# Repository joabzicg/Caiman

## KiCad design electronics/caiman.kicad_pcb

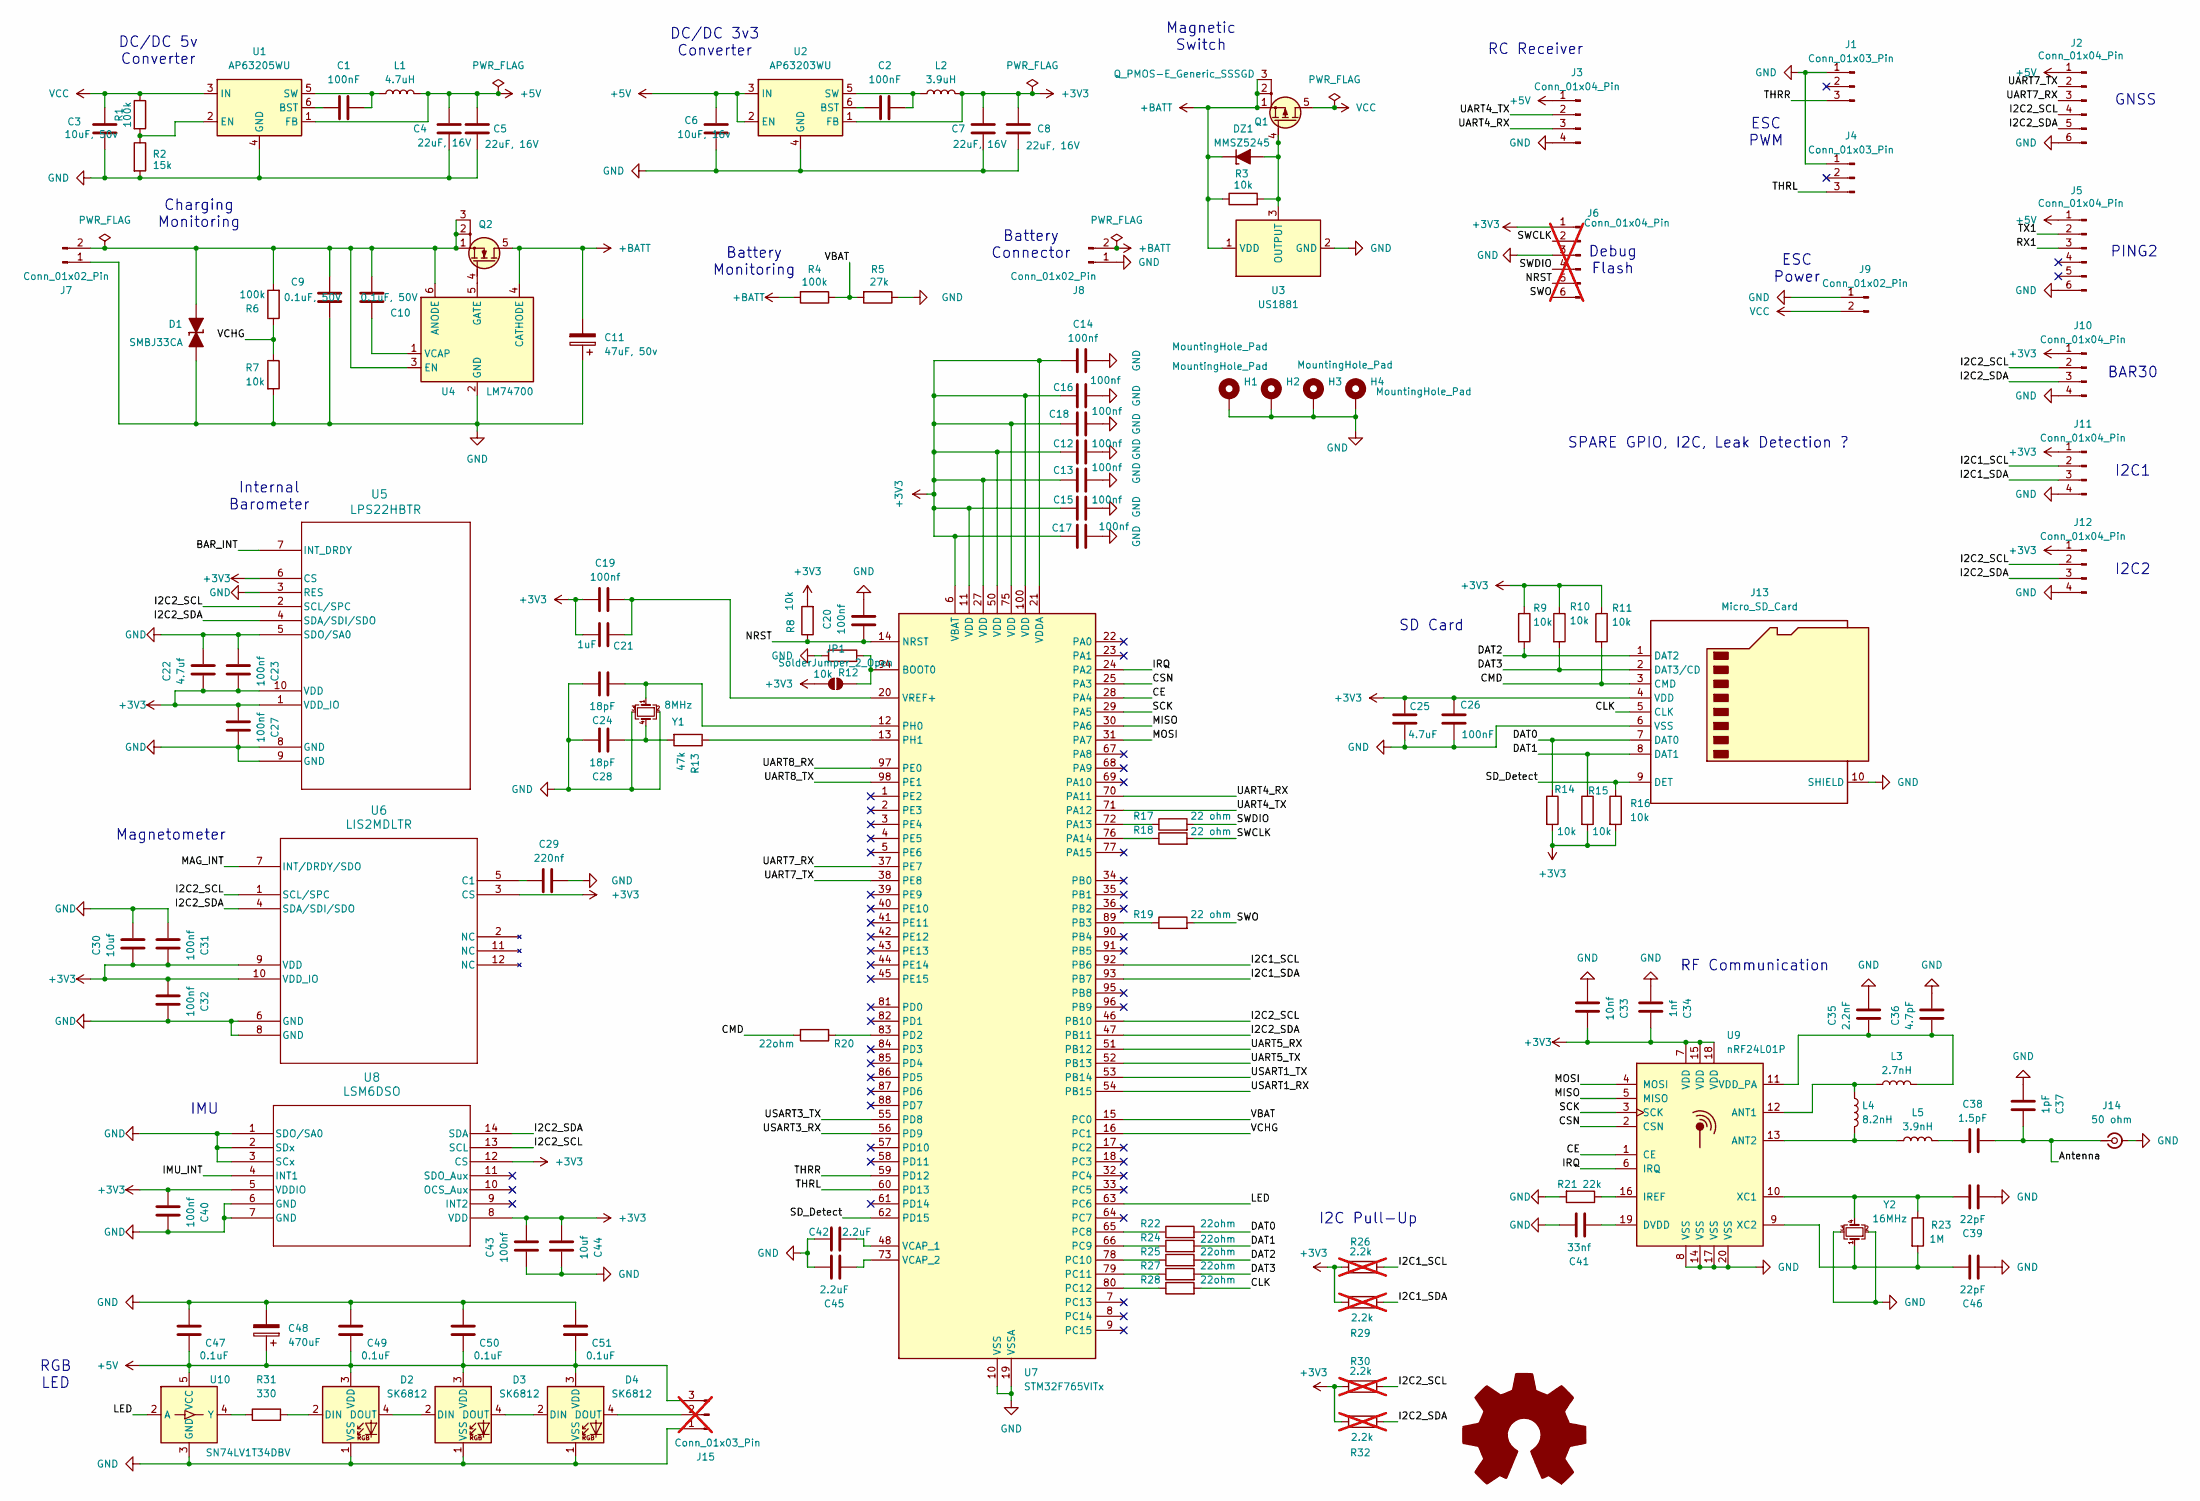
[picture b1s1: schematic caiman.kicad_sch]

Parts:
C1, C2: 100nF; C_0603_1608Metric
C3: 10uF, 50v; C_0805_2012Metric
C4, C5, C7, C8: 22uF, 16V; C_0603_1608Metric
C6: 10uF, 16v; C_0805_2012Metric
C9, C10: 0.1uF, 50V; C_0805_2012Metric
C11: 47uF, 50v; CP_Elec_8x10; Mouser 581-AEA0810470M063R
C12, C13, C14, C15, C16, C17, C18, C19, C20, C23, C27, C31, C32, C40, C43: 100nf; C_0402_1005Metric
C21: 1uF; C_0402_1005Metric
C22: 4.7uf; C_0402_1005Metric
C24, C28: 18pF; C_0402_1005Metric
C25: 4.7uF; C_0402_1005Metric
C26: 100nF; C_0402_1005Metric
C29: 220nf; C_0402_1005Metric
C30, C44: 10uf; C_0402_1005Metric
C33: 10nf; C_0402_1005Metric
C34: 1nf; C_0402_1005Metric
C35: 2.2nF; C_0402_1005Metric
C36: 4.7pF; C_0402_1005Metric
C37: 1pF; C_0402_1005Metric
C38: 1.5pF; C_0402_1005Metric
C39, C46: 22pF; C_0402_1005Metric
C41: 33nf; C_0402_1005Metric
C42, C45: 2.2uF; C_0402_1005Metric
C47, C49, C50, C51: 0.1uF; C_0603_1608Metric
C48: 470uF; CP_Elec_8x10; Mouser 581-AEA0810471M016R
D1: SMBJ33CA; D_SMB_TVS; Mouser 652-SMBJ33CA
D2, D3, D4: SK6812; LED_SK6812_PLCC4_5.0x5.0mm_P3.2mm; Mouser 485-4691
DZ1: MMSZ5245; D_SOD-123F_Zener
H1, H2, H3, H4: MountingHole_Pad; MountingHole_4.3mm_M4_ISO7380_Pad_TopBottom
J1, J4: Conn_01x03_Pin; PinHeader_1x03_P2.54mm_Vertical
J2, J5: Conn_01x04_Pin; JST_GH_BM06B-GHS-TBT_1x06-1MP_P1.25mm_Vertical; Mouser 306-BM06BGHSTBTLFSNN
J3, J10, J11, J12: Conn_01x04_Pin; JST_GH_BM04B-GHS-TBT_1x04-1MP_P1.25mm_Vertical; Mouser 306-BM04BGHSTBTLFSNN
J6: Conn_01x04_Pin; PinHeader_1x06_P2.54mm_Vertical; not fitted
J7: Conn_01x02_Pin; AMASS_XT30UPB-M_1x02_P5.0mm_Vertical; Mouser 426-FIT0587
J8: Conn_01x02_Pin; AMASS_XT60-M_1x02_P7.20mm_Vertical; Mouser 426-FIT0587
J9: Conn_01x02_Pin; AMASS_XT60-F_1x02_P7.20mm_Vertical; Mouser 426-FIT0587
J13: Micro_SD_Card; microSD_HC_Hirose_DM3AT-SF-PEJM5; Mouser 798-DM3ATSFPEJM511
J14: 50 ohm; U.FL_Hirose_U.FL-R-SMT-1_Vertical
J15: Conn_01x03_Pin; PinHeader_1x03_P2.54mm_Vertical; not fitted
JP1: SolderJumper_2_Open; SolderJumper-2_P1.3mm_Open_TrianglePad1.0x1.5mm
L1: 4.7uH; L_Wuerth_MAPI-4020; Mouser 652-SRP4020FA-3R3M
L2: 3.9uH; L_Wuerth_MAPI-4020; Mouser 652-SRP4020FA-2R2M
L3: 2.7nH; L_0402_1005Metric
L4: 8.2nH; L_0402_1005Metric
L5: 3.9nH; L_0402_1005Metric
Q1: Q_PMOS-E_Generic_SSSGD; PowerPAK_SO-8L_Single; Mouser 78-SQJ457EP-T1_GE3
Q2: AON6262E; TDSON-8-1; Digikey 800-3747-2-ND
R1, R4, R6: 100k; R_0603_1608Metric
R2: 15k; R_0603_1608Metric
R3, R7: 10k; R_0603_1608Metric
R5: 27k; R_0603_1608Metric
R8, R9, R10, R11, R12, R14, R15, R16: 10k; R_0402_1005Metric
R13: 47k; R_0402_1005Metric
R17, R18, R19: 22 ohm; R_0402_1005Metric
R20, R22, R24, R25, R27, R28: 22ohm; R_0402_1005Metric
R21: 22k; R_0402_1005Metric
R23: 1M; R_0402_1005Metric
R26, R29, R30, R32: 2.2k; R_0402_1005Metric; not fitted
R31: 330; R_0603_1608Metric
U1: AP63205WU; TSOT-23-6; Mouser 621-AP63205WU-7
U2: AP63203WU; TSOT-23-6; Mouser 621-AP63203WU-7
U3: US1881; TO-92; Mouser 482-1881LUAAAA000BU
U4: LM74700; SOT-23-6; Mouser 595-LM74700QDBVRQ1
U5: LPS22HBTR; ST_HLGA-10_2x2mm_P0.5mm_LayoutBorder3x2y
U6: LIS2MDLTR; LGA-12_2x2mm_P0.5mm
U7: STM32F765VITx; LQFP-100_14x14mm_P0.5mm
U8: LSM6DSO; LGA-14_3x2.5mm_P0.5mm_LayoutBorder3x4y
U9: nRF24L01P; QFN-20-1EP_4x4mm_P0.5mm_EP2.5x2.5mm
U10: SN74LV1T34DBV; SOT-23-5; Mouser 595-SN74LV1T34DBVRG4
Y1: 8MHz; Crystal_SMD_3225-4Pin_3.2x2.5mm
Y2: 16MHz; Crystal_SMD_3225-4Pin_3.2x2.5mm

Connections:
+3V3: C7.2, C8.2, C12.2, C13.2, C14.2, C15.2, C16.2, C17.2, C18.2, C19.2, C21.2, C22.1, C23.1, C25.1, C26.1, C27.2, C30.1, C31.1, C32.2, C33.1, C34.1, C40.2, C43.2, C44.2, J6.1, J10.1, J11.1, J12.1, J13.4 (VDD), JP1.1 (A), L2.2, R8.2, R9.1, R10.1, R11.1, R14.2, R15.2, R16.2, R26.1, R29.1, R30.1, R32.1, U2.1 (FB), U5.1 (VDD_IO), U5.6 (CS), U5.10 (VDD), U6.3 (CS), U6.9 (VDD), U6.10 (VDD_IO), U7.6 (VBAT), U7.11 (VDD), U7.21 (VDDA), U7.27 (VDD), U7.50 (VDD), U7.75 (VDD), U7.100 (VDD), U8.5 (VDDIO), U8.8 (VDD), U8.12 (CS), U9.7 (VDD), U9.15 (VDD), U9.18 (VDD)
+5V: C4.2, C5.2, C6.2, C47.2, C48.1, C49.2, C50.2, C51.2, D2.3 (VDD), D3.3 (VDD), D4.3 (VDD), J2.1, J3.1, J5.1, J15.3, L1.2, U1.1 (FB), U2.2 (EN), U2.3 (IN), U10.5 (VCC)
+BATT: C11.2, DZ1.1 (K), J8.2, Q1.1 (S), Q1.2 (S), Q1.3 (S), Q2.5 (D), R3.1, R4.2, U3.1 (VDD), U4.4 (CATHODE)
/Antenna: C37.2, C38.2, J14.1 (In)
/BAR_INT: U5.7 (INT_DRDY)
/CE: U7.28 (PA4), U9.1 (CE)
/CLK: J13.5 (CLK), R28.2
/CMD: J13.3 (CMD), R11.2, R20.2
/CSN: U7.25 (PA3), U9.2 (CSN)
/DAT0: J13.7 (DAT0), R14.1, R22.2
/DAT1: J13.8 (DAT1), R15.1, R24.2
/DAT2: J13.1 (DAT2), R9.2, R25.2
/DAT3: J13.2 (DAT3/CD), R10.2, R27.2
/I2C1_SCL: J11.2, R26.2, U7.92 (PB6)
/I2C1_SDA: J11.3, R29.2, U7.93 (PB7)
/I2C2_SCL: J2.4, J10.2, J12.2, R30.2, U5.2 (SCL/SPC), U6.1 (SCL/SPC), U7.46 (PB10), U8.13 (SCL)
/I2C2_SDA: J2.5, J10.3, J12.3, R32.2, U5.4 (SDA/SDI/SDO), U6.4 (SDA/SDI/SDO), U7.47 (PB11), U8.14 (SDA)
/IMU_INT: U8.4 (INT1)
/IRQ: U7.24 (PA2), U9.6 (IRQ)
/LED: U7.63 (PC6), U10.2 (A)
/MAG_INT: U6.7 (INT/DRDY/SDO)
/MISO: U7.30 (PA6), U9.5 (MISO)
/MOSI: U7.31 (PA7), U9.4 (MOSI)
/NRST: C20.2, J6.5, R8.1, U7.14 (NRST)
/RX1: J5.3
/SCK: U7.29 (PA5), U9.3 (SCK)
/SD_Detect: J13.9 (DET), R16.1, U7.62 (PD15)
/SWCLK: J6.2, R18.2
/SWDIO: J6.4, R17.2
/SWO: J6.6, R19.2
/THRL: J4.3, U7.60 (PD13)
/THRR: J1.3, U7.59 (PD12)
/TX1: J5.2
/UART4_RX: J3.3, U7.70 (PA11)
/UART4_TX: J3.2, U7.71 (PA12)
/UART5_RX: U7.51 (PB12)
/UART5_TX: U7.52 (PB13)
/UART7_RX: J2.3, U7.37 (PE7)
/UART7_TX: J2.2, U7.38 (PE8)
/UART8_RX: U7.97 (PE0)
/UART8_TX: U7.98 (PE1)
/USART1_RX: U7.54 (PB15)
/USART1_TX: U7.53 (PB14)
/USART3_RX: U7.56 (PD9)
/USART3_TX: U7.55 (PD8)
/VBAT: R4.1, R5.2, U7.15 (PC0)
/VCHG: R6.1, R7.1, U7.16 (PC1)
unnamed: C38.1, L5.2
unnamed: C9.1, C10.2, D1.2 (A), J7.2, Q2.1 (S), Q2.2 (S), Q2.3 (S), R6.2, U4.3 (EN), U4.6 (ANODE)
unnamed: D2.2 (DIN), R31.2
unnamed: D2.4 (DOUT), D3.2 (DIN)
unnamed: D3.4 (DOUT), D4.2 (DIN)
unnamed: D4.4 (DOUT), J15.2
unnamed: DZ1.2 (A), Q1.4 (G), R3.2, U3.3 (OUTPUT)
unnamed: JP1.2 (B), R12.1, U7.94 (BOOT0)
unnamed: Q2.4 (G), U4.5 (GATE)
unnamed: C1.2, U1.6 (BST)
unnamed: R1.2, R2.1, U1.2 (EN)
unnamed: C1.1, L1.1, U1.5 (SW)
unnamed: C2.2, U2.6 (BST)
unnamed: C2.1, L2.1, U2.5 (SW)
unnamed: C10.1, U4.1 (VCAP)
unnamed: C29.2, U6.5 (C1)
unnamed: R17.1, U7.72 (PA13)
unnamed: R18.1, U7.76 (PA14)
unnamed: R19.1, U7.89 (PB3)
unnamed: R22.1, U7.65 (PC8)
unnamed: R24.1, U7.66 (PC9)
unnamed: R25.1, U7.78 (PC10)
unnamed: R27.1, U7.79 (PC11)
unnamed: R28.1, U7.80 (PC12)
unnamed: R20.1, U7.83 (PD2)
unnamed: C24.2, U7.12 (PH0), Y1.1
unnamed: R13.1, U7.13 (PH1)
unnamed: C42.1, U7.48 (VCAP_1)
unnamed: C45.2, U7.73 (VCAP_2)
unnamed: C19.1, C21.1, U7.20 (VREF+)
unnamed: L3.1, L4.1, U9.12 (ANT1)
unnamed: L4.2, L5.1, U9.13 (ANT2)
unnamed: C41.2, U9.19 (DVDD)
unnamed: R21.1, U9.16 (IREF)
unnamed: C35.1, C36.1, L3.2, U9.11 (VDD_PA)
unnamed: C46.1, R23.2, U9.9 (XC2), Y2.1
unnamed: R31.1, U10.4 (Y)
VCC: C3.2, J9.2, Q1.5 (D), R1.1, U1.3 (IN)

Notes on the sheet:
GNSS
RGB LED
Magnetic Switch
Charging Monitoring
IMU
SD Card
SPARE GPIO, I2C, Leak Detection ?
PING2
Magnetometer
RC Receiver
BAR30
RF Communication
Internal Barometer
ESC Power
Battery Connector
I2C1
Battery Monitoring
I2C2
Debug Flash
DC/DC 5v Converter
I2C Pull-Up
ESC PWM
DC/DC 3v3 Converter

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
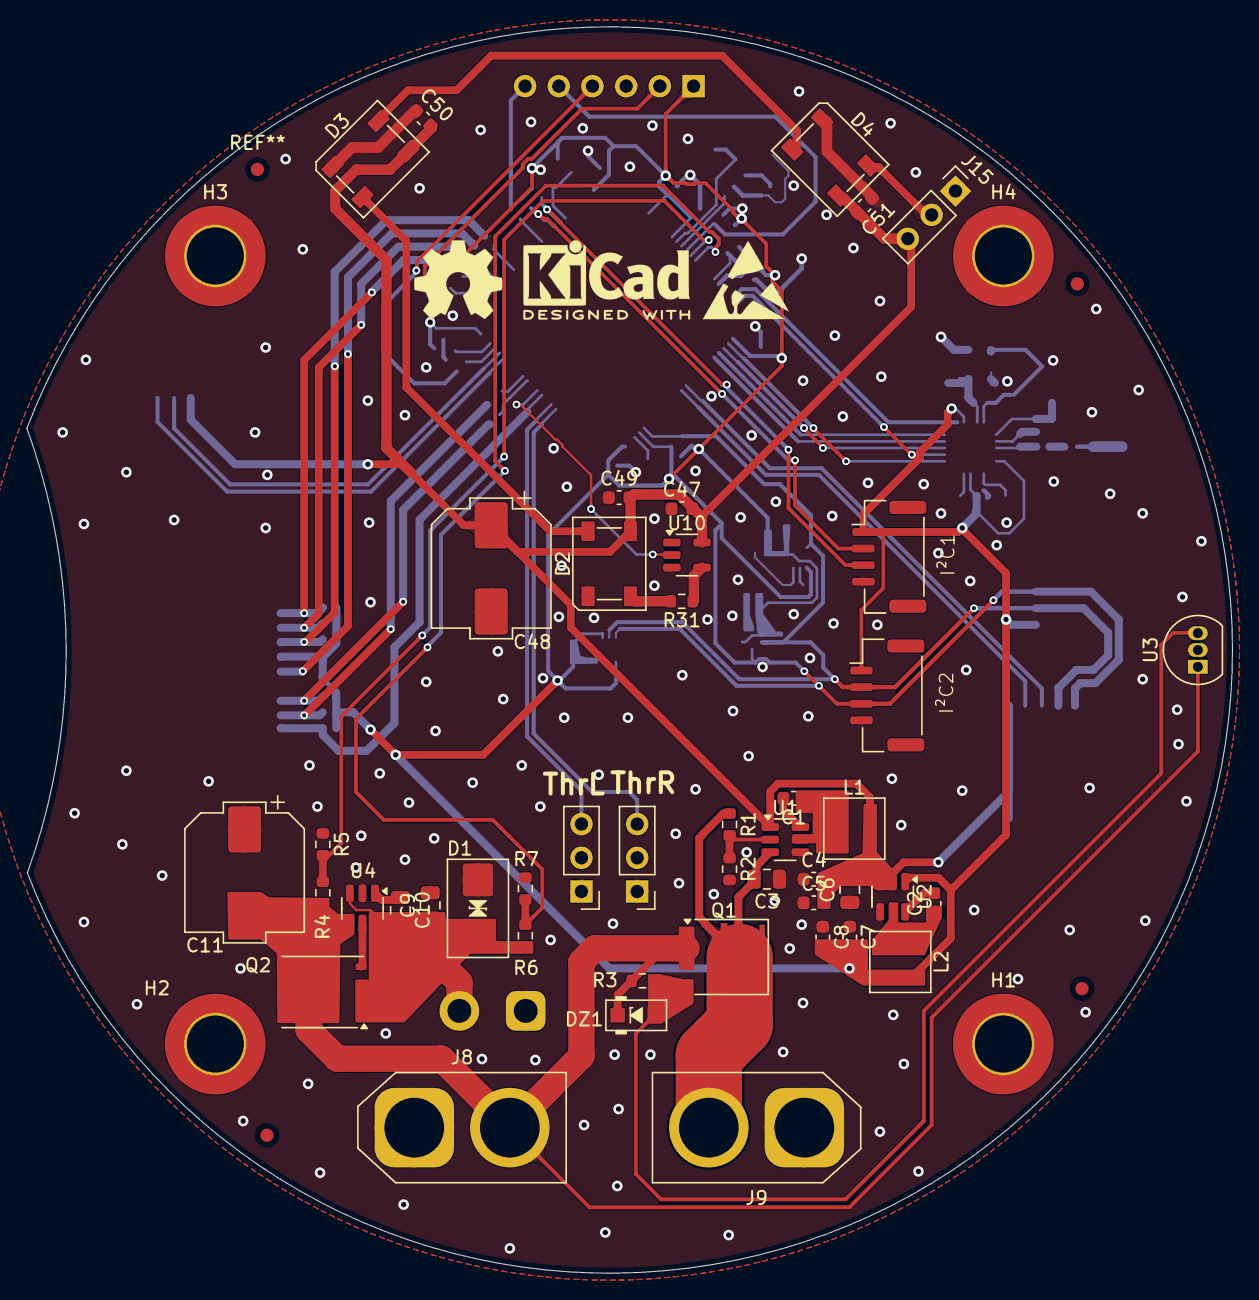
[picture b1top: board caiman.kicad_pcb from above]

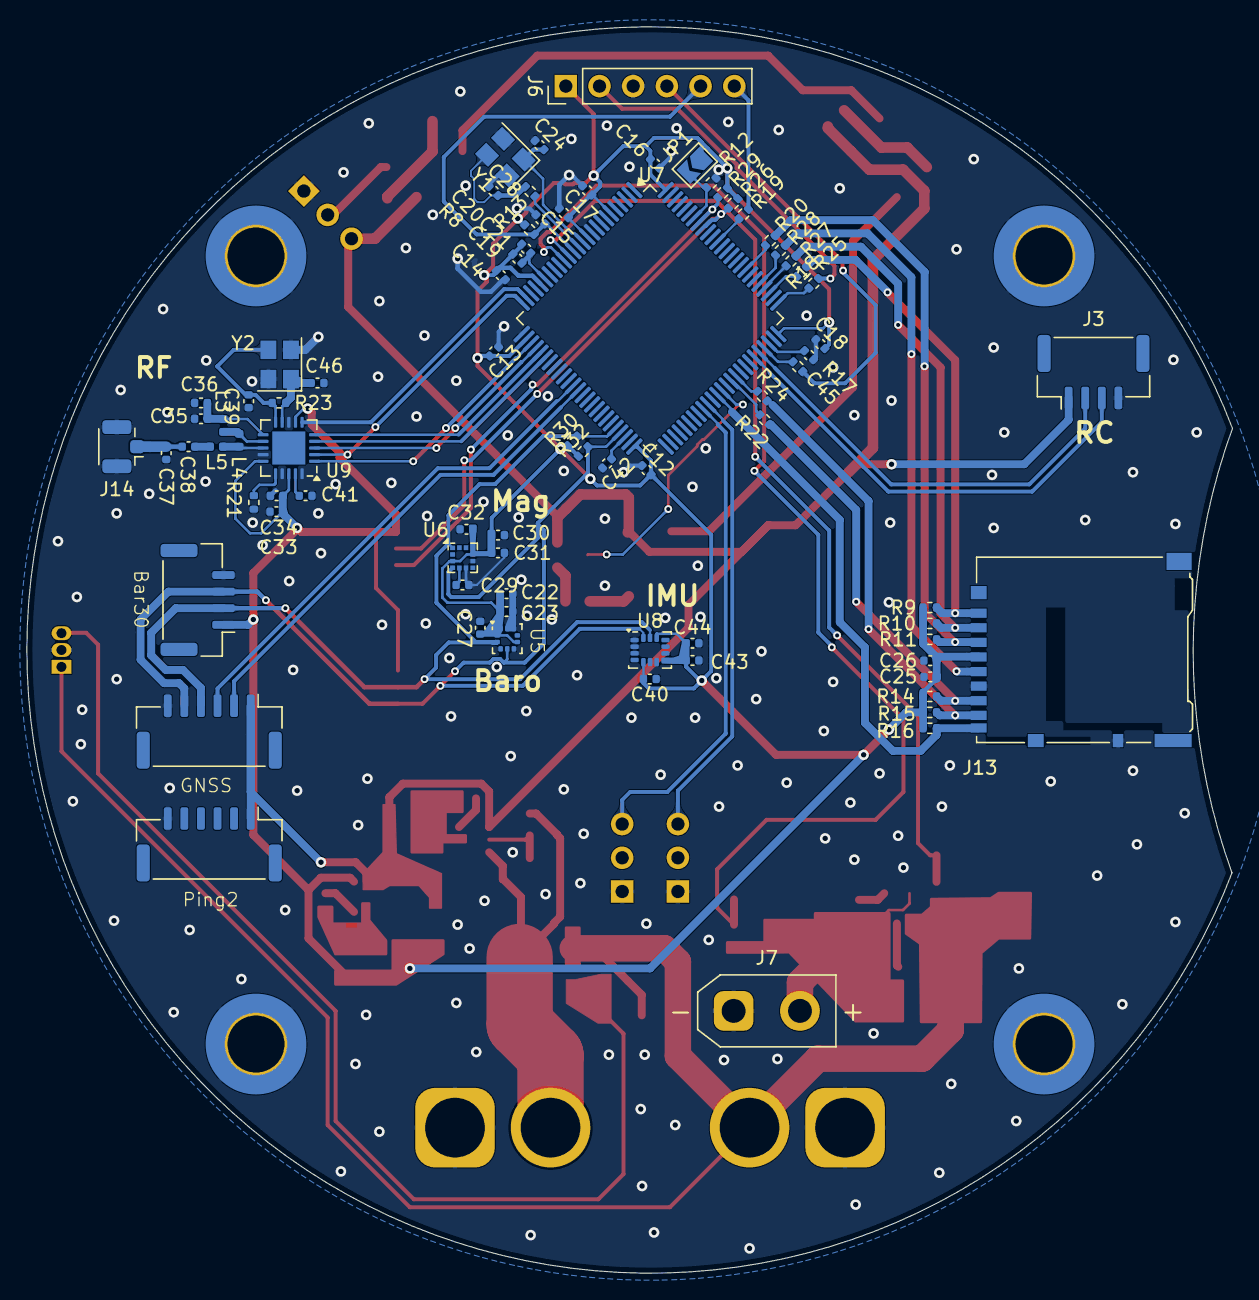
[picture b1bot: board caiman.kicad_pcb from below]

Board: 2 copper layers, 90.9 x 93.9 mm, 127 parts (78 on the bottom side), 75 nets.

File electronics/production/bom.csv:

Designator,Footprint,Quantity,Value,LCSC Part #
"_3, _2, ",,3,,
"C1, C2",0603,2,100nF,
"C10, C9",0805,2,"0.1uF, 50V",
C11,CP_Elec_8x10,1,"47uF, 50v",
"C12, C13, C14, C15, C16, C17, C18, C19, C20, C23, C26, C27, C31, C32, C40, C43",0402,16,100nf,
C21,0402,1,1uF,
"C22, C25",0402,2,4.7uf,
"C24, C28",0402,2,18pF,
C29,0402,1,220nf,
C3,0805,1,"10uF, 50v",
"C30, C44",0402,2,10uf,
C33,0402,1,10nf,
C34,0402,1,1nf,
C35,0402,1,2.2nF,
C36,0402,1,4.7pF,
C37,0402,1,1pF,
C38,0402,1,1.5pF,
"C39, C46",0402,2,22pF,
"C4, C5, C7, C8",0603,4,"22uF, 16V",
C41,0402,1,33nf,
"C42, C45",0402,2,2.2uF,
"C47, C49, C50, C51",0603,4,0.1uF,
C48,CP_Elec_8x10,1,470uF,
C6,0805,1,"10uF, 16v",
D1,D_SMB_TVS,1,SMBJ33CA,
"D2, D3, D4",LED_SK6812_PLCC4_5.0x5.0mm_P3.2mm,3,SK6812,
DZ1,D_SOD-123F_Zener,1,MMSZ5245,
"J1, J4",PinHeader_1x03_P2.54mm_Vertical,2,Conn_01x03_Pin,
"J10, J11, J12, J3",JST_GH_BM04B-GHS-TBT_1x04-1MP_P1.25mm_Vertical,4,Conn_01x04_Pin,
J13,microSD_HC_Hirose_DM3AT-SF-PEJM5,1,Micro_SD_Card,
J14,U.FL_Hirose_U.FL-R-SMT-1_Vertical,1,50 ohm,
"J2, J5",JST_GH_BM06B-GHS-TBT_1x06-1MP_P1.25mm_Vertical,2,Conn_01x04_Pin,
J7,AMASS_XT30UPB-M_1x02_P5.0mm_Vertical,1,Conn_01x02_Pin,
J8,AMASS_XT60-M_1x02_P7.20mm_Vertical,1,Conn_01x02_Pin,
J9,AMASS_XT60-F_1x02_P7.20mm_Vertical,1,Conn_01x02_Pin,
L1,L_Wuerth_MAPI-4020,1,4.7uH,
L2,L_Wuerth_MAPI-4020,1,3.9uH,
L3,0402,1,2.7nH,
L4,0402,1,8.2nH,
L5,0402,1,3.9nH,
Q1,PowerPAK_SO-8L_Single,1,Q_PMOS-E_Generic_SSSGD,
Q2,TDSON-8-1,1,AON6262E,
"R1, R4, R6",0603,3,100k,
"R10, R11, R12, R14, R15, R16, R8, R9",0402,8,10k,
R13,0402,1,47k,
"R17, R18, R19",0402,3,22 ohm,
R2,0603,1,15k,
"R20, R22, R24, R25, R27, R28",0402,6,22ohm,
R21,0402,1,22k,
R23,0402,1,1M,
"R3, R7",0603,2,10k,
R31,0603,1,330,
R5,0603,1,27k,
U1,TSOT-23-6,1,AP63205WU,
U10,SOT-23-5,1,SN74LV1T34DBV,
U2,TSOT-23-6,1,AP63203WU,
U3,TO-92,1,US1881,
U4,SOT-23-6,1,LM74700,
U5,ST_HLGA-10_2x2mm_P0.5mm_LayoutBorder3x2y,1,LPS22HBTR,
U6,LGA-12_2x2mm_P0.5mm,1,LIS2MDLTR,
U7,LQFP-100_14x14mm_P0.5mm,1,STM32F765VITx,
U8,LGA-14_3x2.5mm_P0.5mm_LayoutBorder3x4y,1,LSM6DSO,
U9,QFN-20-1EP_4x4mm_P0.5mm_EP2.5x2.5mm,1,nRF24L01P,
Y1,Crystal_SMD_3225-4Pin_3.2x2.5mm,1,8MHz,
Y2,Crystal_SMD_3225-4Pin_3.2x2.5mm,1,16MHz,

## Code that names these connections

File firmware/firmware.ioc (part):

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Mcu.Name=STM32F765V(G-I)Tx
Mcu.Package=LQFP100
Mcu.UserName=STM32F765VITx
PA0/WKUP.Signal=ADCx_IN0
PA1.Signal=ADCx_IN1
PA11.Mode=Asynchronous
PA11.Signal=UART4_RX
PA12.Mode=Asynchronous
PA12.Signal=UART4_TX
PA13.Mode=Trace_Asynchronous_SW
PA13.Signal=SYS_JTMS-SWDIO
PA14.Mode=Trace_Asynchronous_SW
PA14.Signal=SYS_JTCK-SWCLK
PA5.Mode=Full_Duplex_Master
PA5.Signal=SPI1_SCK
PA6.Mode=Full_Duplex_Master
PA6.Signal=SPI1_MISO
PA7.Mode=Full_Duplex_Master
PA7.Signal=SPI1_MOSI
PB10.Mode=I2C
PB10.Signal=I2C2_SCL
PB11.Mode=I2C
PB11.Signal=I2C2_SDA
PB12.Mode=Asynchronous
PB12.Signal=UART5_RX
PB13.Mode=Asynchronous
PB13.Signal=UART5_TX
PB14.Mode=Asynchronous
PB14.Signal=USART1_TX
PB15.Mode=Asynchronous
PB15.Signal=USART1_RX
PB3.Mode=Trace_Asynchronous_SW
PB3.Signal=SYS_JTDO-SWO
PB6.Mode=I2C
PB6.Signal=I2C1_SCL
PB7.Mode=I2C
PB7.Signal=I2C1_SDA
PC10.Mode=SD_4_bits_Wide_bus
PC10.Signal=SDMMC1_D2
PC11.Mode=SD_4_bits_Wide_bus
PC11.Signal=SDMMC1_D3
PC12.Mode=SD_4_bits_Wide_bus
PC12.Signal=SDMMC1_CK
PC6.GPIOParameters=GPIO_Label
PC6.GPIO_Label=LED
PC6.Signal=S_TIM3_CH1
PC8.Mode=SD_4_bits_Wide_bus
PC8.Signal=SDMMC1_D0
PC9.Mode=SD_4_bits_Wide_bus
PC9.Signal=SDMMC1_D1
PD12.GPIOParameters=GPIO_Label
PD12.GPIO_Label=THRR
PD12.Signal=S_TIM4_CH1
PD13.GPIOParameters=GPIO_Label
PD13.GPIO_Label=THRL
PD13.Signal=S_TIM4_CH2
PD15.GPIOParameters=GPIO_Label
PD15.GPIO_Label=SD_Detect
PD15.Signal=GPIO_Input
PD2.Mode=SD_4_bits_Wide_bus
PD2.Signal=SDMMC1_CMD
PD8.Mode=Asynchronous
PD8.Signal=USART3_TX
PD9.Mode=Asynchronous
PD9.Signal=USART3_RX
PE0.Mode=Asynchronous
PE0.Signal=UART8_RX
PE1.Mode=Asynchronous
PE1.Signal=UART8_TX
PE7.Mode=Asynchronous
PE7.Signal=UART7_RX
PE8.Mode=Asynchronous
PE8.Signal=UART7_TX
RCC.HSE_VALUE=25000000
board=custom

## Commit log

2026-05-12 Electronic PCB
2026-05-12 Adding README.md
2026-06-01 Updating the PCB
2026-06-01 Adding firmware
2026-06-03 STM32 Power Supply correction
    Modified series capacitors to parallel capacitors in STM32
2026-06-03 [SYMB/MODELS] Change GND type port LSM6DSO
    Change GND port to power supply input.
2026-06-03 [SCHEMATICS] Duplicated Power Flags removal
    Removal of duplicated power flags symbols, and added at the VSS of RGBLED's.
2026-06-08 DRC Clean
2026-06-09 final DRC verification
    finished for fabrication
2026-06-10 Drivers implementation
    Firmware implementation and simulation in wokwi.
2026-06-19 [Schm & PCB] Footprint correction
2026-06-23 Finalization of PCB
